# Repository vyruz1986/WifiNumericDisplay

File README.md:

# WiFi numeric display

## Introduction

This project is a generic 4-digit 7-segment numeric display which can be controlled over WiFi.
It uses a Wemos D1 Mini MCU and TPIC6B595 power logic shift registers to control pieces of powerful, very bright 24V LED strip segments.
These displays are highly visible even in bright sunlight over a long distance (used in Fyball competitions where viewing distance is around 30 meters).

It was created for use in Flyball, but can easily be applied elsewhere

Pictures & video: https://goo.gl/photos/G3tg8hrfvAJZ6PEY8

## Hardware

-Under construction-

Basically this is a 'beefed up' version of [Sparkfun's large 7 segment displays](https://www.sparkfun.com/products/8530)
together with [Sparkfun's accompanying large digit driver boards](https://www.sparkfun.com/products/13279).

The code is 1:1 compatible, the difference with my project is that I use the following components
to allow for better visibility (moar light!):

|Part type			| Sparkfun part						| My Part																	| Description																|
| ----------------- | --------------------------------- | ------------------------------------------------------------------------- | ------------------------------------------------------------------------- |
| Digit segment		| [12 SMD LEDs per segment (200mcd)](https://www.sparkfun.com/datasheets/Components/YSD-1600AR6F-89.pdf) driven with 12V	| 10cm of [24V 240 LED/meter strip](http://s.click.aliexpress.com/e/3zjiyZV)	| These are larger, more powerful LEDs which are also denser positioned.	|
| Segment driver	| [TPIC6C596](https://cdn.sparkfun.com/datasheets/Widgets/TPIC6C596.pdf) | [TPIC6B595](https://www.reichelt.de/?ACTION=3;ARTICLE=147328;SEARCH=tpic) | Compatible chip which can handle the extra current that out LED strip segments will draw |

I will complete this section later with a description on how to make the display using 10cm LED strip pieces and an aluminium plate to mount them on.

## Flashing the firmware

The firmware should flash just fine using the Arduino IDE with ESP8266 support. Open the `SevenSegmentDisplay.ino` file, select Wemos D1 mini as the board and hit flash.

You might want to change the OTA flash password in the `SevenSegmentDisplay.ino` file, search for the following line:
`#define OTA_PASSWD "EnterUniquePasswordHere!"`

## Connection & protocol

### Connecting to the display

The display listens on TCP port 23, no authentication is currently supported. Up to 5 clients can be connected simultaneously.

### Supported messages

Currently 2 messages are supported:

* `CDnnnn`: Where `nnnn` is a number between 0 and 9999. This message will start a countdown of the given number in seconds.
* `nnnn`: Where `nnnn` is a number between 0 and 9999. The number is expected to be an amount of time in hundredths of seconds. The time will be displayed in the format of SS.ss. e.g. sending `1234`, the display will show 12.34

Each message should be terminated by a newline (`\n`).

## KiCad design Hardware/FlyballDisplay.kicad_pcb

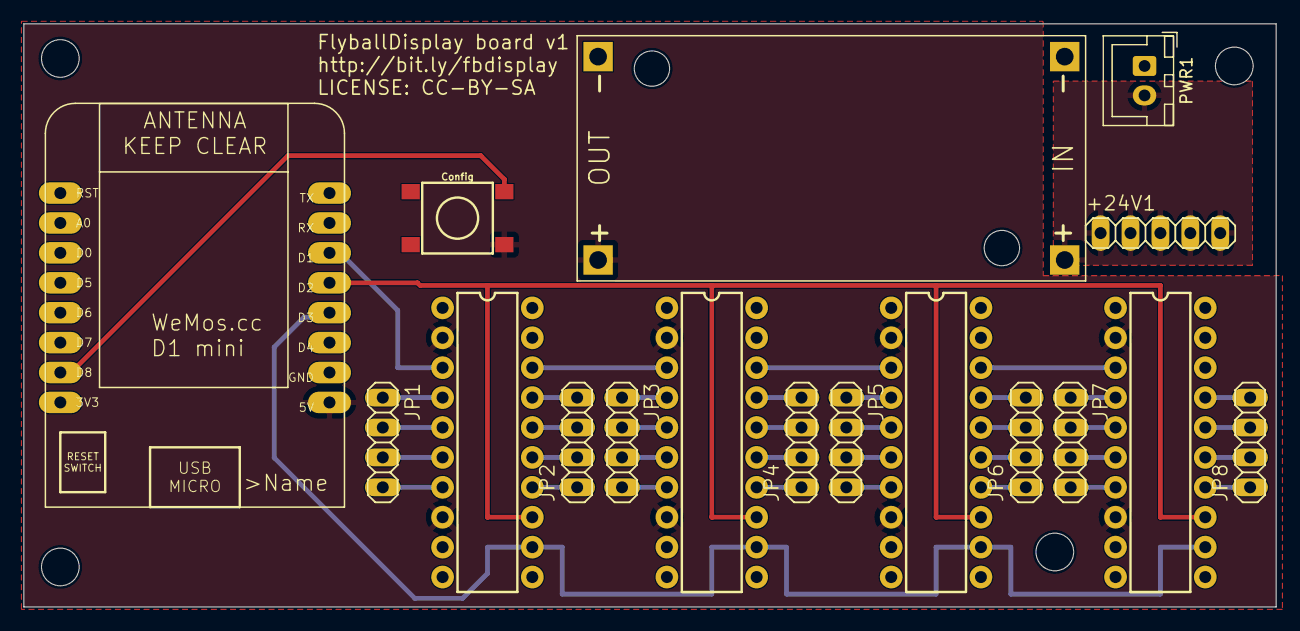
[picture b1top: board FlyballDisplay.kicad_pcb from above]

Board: 2 copper layers, 106.3 x 49.5 mm, 18 parts (0 on the bottom side), 42 nets.

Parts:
+24V1: PINHD-1X5; 1X05
JP1, JP2, JP3, JP4, JP5, JP6, JP7, JP8: PINHD-1X4; 1X04
PWR1: 02-JST; JST_XH_B2B-XH-A_1x02_P2.50mm_Vertical
S1: MOMENTARY-SWITCH-SPST-SMD-6.2MM-TALL; TACTILE_SWITCH_SMD_6.2MM_TALL
U1, U2, U3, U4: TPIC6B595PTH; DIL20
U$1: DC-DC-STEP-DOWN-LM2596
U$2: A4L-LOC
WEMOS1: WEMOS-D1-MINI

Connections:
+5V: S1.A2 (1), U1.2 (VCC), U1.8 (~SRCLR), U2.2 (VCC), U2.8 (~SRCLR), U3.2 (VCC), U3.8 (~SRCLR), U4.2 (VCC), U4.8 (~SRCLR), U$1.OUT+, WEMOS1.5V
+24V: +24V1.1, +24V1.2, +24V1.3, +24V1.4, +24V1.5, PWR1.2, U$1.IN+
/CLOCK: U1.13 (SRCK), U2.13 (SRCK), U3.13 (SRCK), U4.13 (SRCK), WEMOS1.D2
/LATCH: U1.12 (RCK), U2.12 (RCK), U3.12 (RCK), U4.12 (RCK), WEMOS1.D3
GND: PWR1.1, U1.9 (~G), U1.10 (GND@10), U1.11 (GND@11), U1.19 (GND@19), U2.9 (~G), U2.10 (GND@10), U2.11 (GND@11), U2.19 (GND@19), U3.9 (~G), U3.10 (GND@10), U3.11 (GND@11), U3.19 (GND@19), U4.9 (~G), U4.10 (GND@10), U4.11 (GND@11), U4.19 (GND@19), U$1.IN-, U$1.OUT-, WEMOS1.GND
unnamed: JP1.1, U1.4 (D0)
unnamed: JP1.2, U1.5 (D1)
unnamed: JP1.3, U1.6 (D2)
unnamed: JP1.4, U1.7 (D3)
unnamed: JP2.1, U1.14 (D4)
unnamed: JP2.2, U1.15 (D5)
unnamed: JP2.3, U1.16 (D6)
unnamed: JP2.4, U1.17 (D7)
unnamed: JP3.1, U2.4 (D0)
unnamed: JP3.2, U2.5 (D1)
unnamed: JP3.3, U2.6 (D2)
unnamed: JP3.4, U2.7 (D3)
unnamed: JP4.1, U2.14 (D4)
unnamed: JP4.2, U2.15 (D5)
unnamed: JP4.3, U2.16 (D6)
unnamed: JP4.4, U2.17 (D7)
unnamed: JP5.1, U3.4 (D0)
unnamed: JP5.2, U3.5 (D1)
unnamed: JP5.3, U3.6 (D2)
unnamed: JP5.4, U3.7 (D3)
unnamed: JP6.1, U3.14 (D4)
unnamed: JP6.2, U3.15 (D5)
unnamed: JP6.3, U3.16 (D6)
unnamed: JP6.4, U3.17 (D7)
unnamed: JP7.1, U4.4 (D0)
unnamed: JP7.2, U4.5 (D1)
unnamed: JP7.3, U4.6 (D2)
unnamed: JP7.4, U4.7 (D3)
unnamed: JP8.1, U4.14 (D4)
unnamed: JP8.2, U4.15 (D5)
unnamed: JP8.3, U4.16 (D6)
unnamed: JP8.4, U4.17 (D7)
unnamed: S1.B2 (2), WEMOS1.D8
unnamed: U1.3 (SER_IN), WEMOS1.D1
unnamed: U1.18 (SER_OUT), U2.3 (SER_IN)
unnamed: U2.18 (SER_OUT), U3.3 (SER_IN)
unnamed: U3.18 (SER_OUT), U4.3 (SER_IN)

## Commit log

2018-03-20 Added README describing the project
2018-03-21 Added GPL license statements
2018-03-21 Updated README to talk a bit about the hardware
2018-03-21 Added link to google photos album in README
2018-03-21 More documentation
2021-04-05 feat: Removed Syslog library
2021-04-06 refactor: Moved project to PlatformIO
2021-04-07 fix: Use latest espressif lib and high upload speed
2021-04-07 feat: Added hardware folder with Kicad schematics and board files
2022-03-19 fix: Replaced JST XH header with correct hole size and updated to KiCAD 6

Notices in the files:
Hardware/FlyballDisplay.kicad_pcb:
LICENSE: CC-BY-SA
